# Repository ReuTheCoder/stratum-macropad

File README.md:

# Stratum 
Stratum is a 9-key personal macropad creation with a rotary encoder, an OLED display and RGB backlighting under each key that uses QMK firmware. It supports five independent layers, allowing each key to perform a unique function depending on the active layer. Stratum was made as a submission for [Hackpad v5](https://hackpad.hackclub.com/) through HackClub's Stardance Challenge.

## Features:
- 0.91 inch OLED display
- A EC11 Rotary encoder (push button diabled)
- 9 MX-Style switches with DSA keycaps
- 9 accompanying SK6812 MINI-E LEDs for backlighting

## PCB
This is the PCB I made for Stratum; made in KiCad 10.0. Most of the footprints were provided by HackClub. Anything else was from KICad's default libraries or was sourced through peers on the HackClub Slack. The silkscreen uses HackClub's logo and a character from the Stardance Challenge.

**Schematic:**

**PCB:**

## CAD Model
This CAD model, designed in Fusion 360, utilizes an integrated plate keyboard mount style - so it only has a top and bottom piece that are connected together with four 16mm M3 bolts that are screwed in from the bottom of the case. Right now, the case relies on self-threading since I don't anticipate needing to unscrew the macropad often after assembly. Realistically, I have noted I will need to add heat-set inserts in a future version to ensure its long-term survival. The rotary encoder cap was provided by HackClub. 

## Firmware Overview
The name Stratum reflects this macropad's ability to swap between 5 distinct layers through QMK firmware. This is done through a Settings mode in which you must hold down three center keys until the OLED displays a selection menu where you can use the rotary encoder to scroll through the 5 different layers. You select with the lower-right key. An overview of notable firmware features are:

- 5 Different Layers: Main, Productivity, Design, Scientific and Media. The keys and rotary encoder change functions on each mode
- The OLED that displays current layer, settings menu and a transition animation
- RGB Backlights change color on each layer
- A sleep and brightness control in settings
- Rotary encoder volume control

The 5 layers will likely be updated as I use the macropad and see what does and does not work. A future idea I have in mind is adding VIA support for quick macro functionality edits.

## Bill of Materials [BOM]:
All the components needed for this macropad design:
- 9x Cherry MX Switches
- 9x DSA Keycaps
- 4x M3x16mm screws
- 9x through-hole 1N4148 Diodes
- 9x SK6812 MINI-E LEDs (reverse mount)
- 1x 0.91 inch OLED display (128x32)
- 1x EC11 Rotary encoder
- 1x XIAO RP2040
- 1x Case (2 printed parts + optional Rotary Encoder Cap)
  
## Additional Notes
This was my first time completely designing a piece of hardware from scratch. I used this project as an opportunity to learn PCB design through KiCad (both things I have never done before) and become accustomed to a new CAD program (before this, I had only used Tinkercad for 3D printing). This project also served as an introduction to QMK firmware. Although this project greatly increased my understanding of it (as I already had some experience coding arduino in C++), I still need more time writing QMK firmware to become comfortably familiar with it (I had a lot of external help when writing my firmware). Although it seemed to compile correctly, I have no idea if it will work as expected once I flash it to the RP2040. 

### Firmware Layer-Specific Functions
Layer 0 - Main <br>
&emsp;       K1 Save | K2  (close/escape) | K3 Refresh <br>
&emsp;       K4 File Explorer | K5 Settings | K6 Task Manager <br>
&emsp;       K7 Emoji Panel | K8 Screenshot | K9 Calculator <br>

Layer 1 - Productivity (Docs) <br>
&emsp;    K1 Citations | K2  Spell Check| K3 Clear Formatting <br>
&emsp;     K4 Align Left| K5 Center | K6 Align Right <br>
&emsp;     K7 Find | K8 Insert Link| K9 Print <br>

Layer 2 -  Design <br>
&emsp;     K1 Undo | K2 Redo | K3 Duplicate <br>
&emsp;     K4 Group | K5 Ungroup | K6 Bring Forward <br>
&emsp;     K7 Zoom In | K8 Zoom Out  | K9 Fit Screen <br>

Layer 3 -  Scientific (Docs) <br>
&emsp;     K1 ° | K2 ±  | K3 × <br>
&emsp;     K4 √  |  K5 π  | K6 Σ <br>
&emsp;     K7 Superscript | K8 Subscript  | K9 Open Latex Editor <br>

Layer 4 -  Media <br>
&emsp;     K1 Play  | K2 Pause  | K3 Stop <br>
&emsp;     K4 Previous  |  K5 Next  | K6 Mute <br>
&emsp;     K7 Spotify | K8 Youtube | K9 Libby (Audiobook App) <br>

Thank you so much to @qcoral and the rest of the organizers of [Stardance](https://stardance.hackclub.com/missions/hackpad) and HackClub for this wonderful hardware exploration opportunity!

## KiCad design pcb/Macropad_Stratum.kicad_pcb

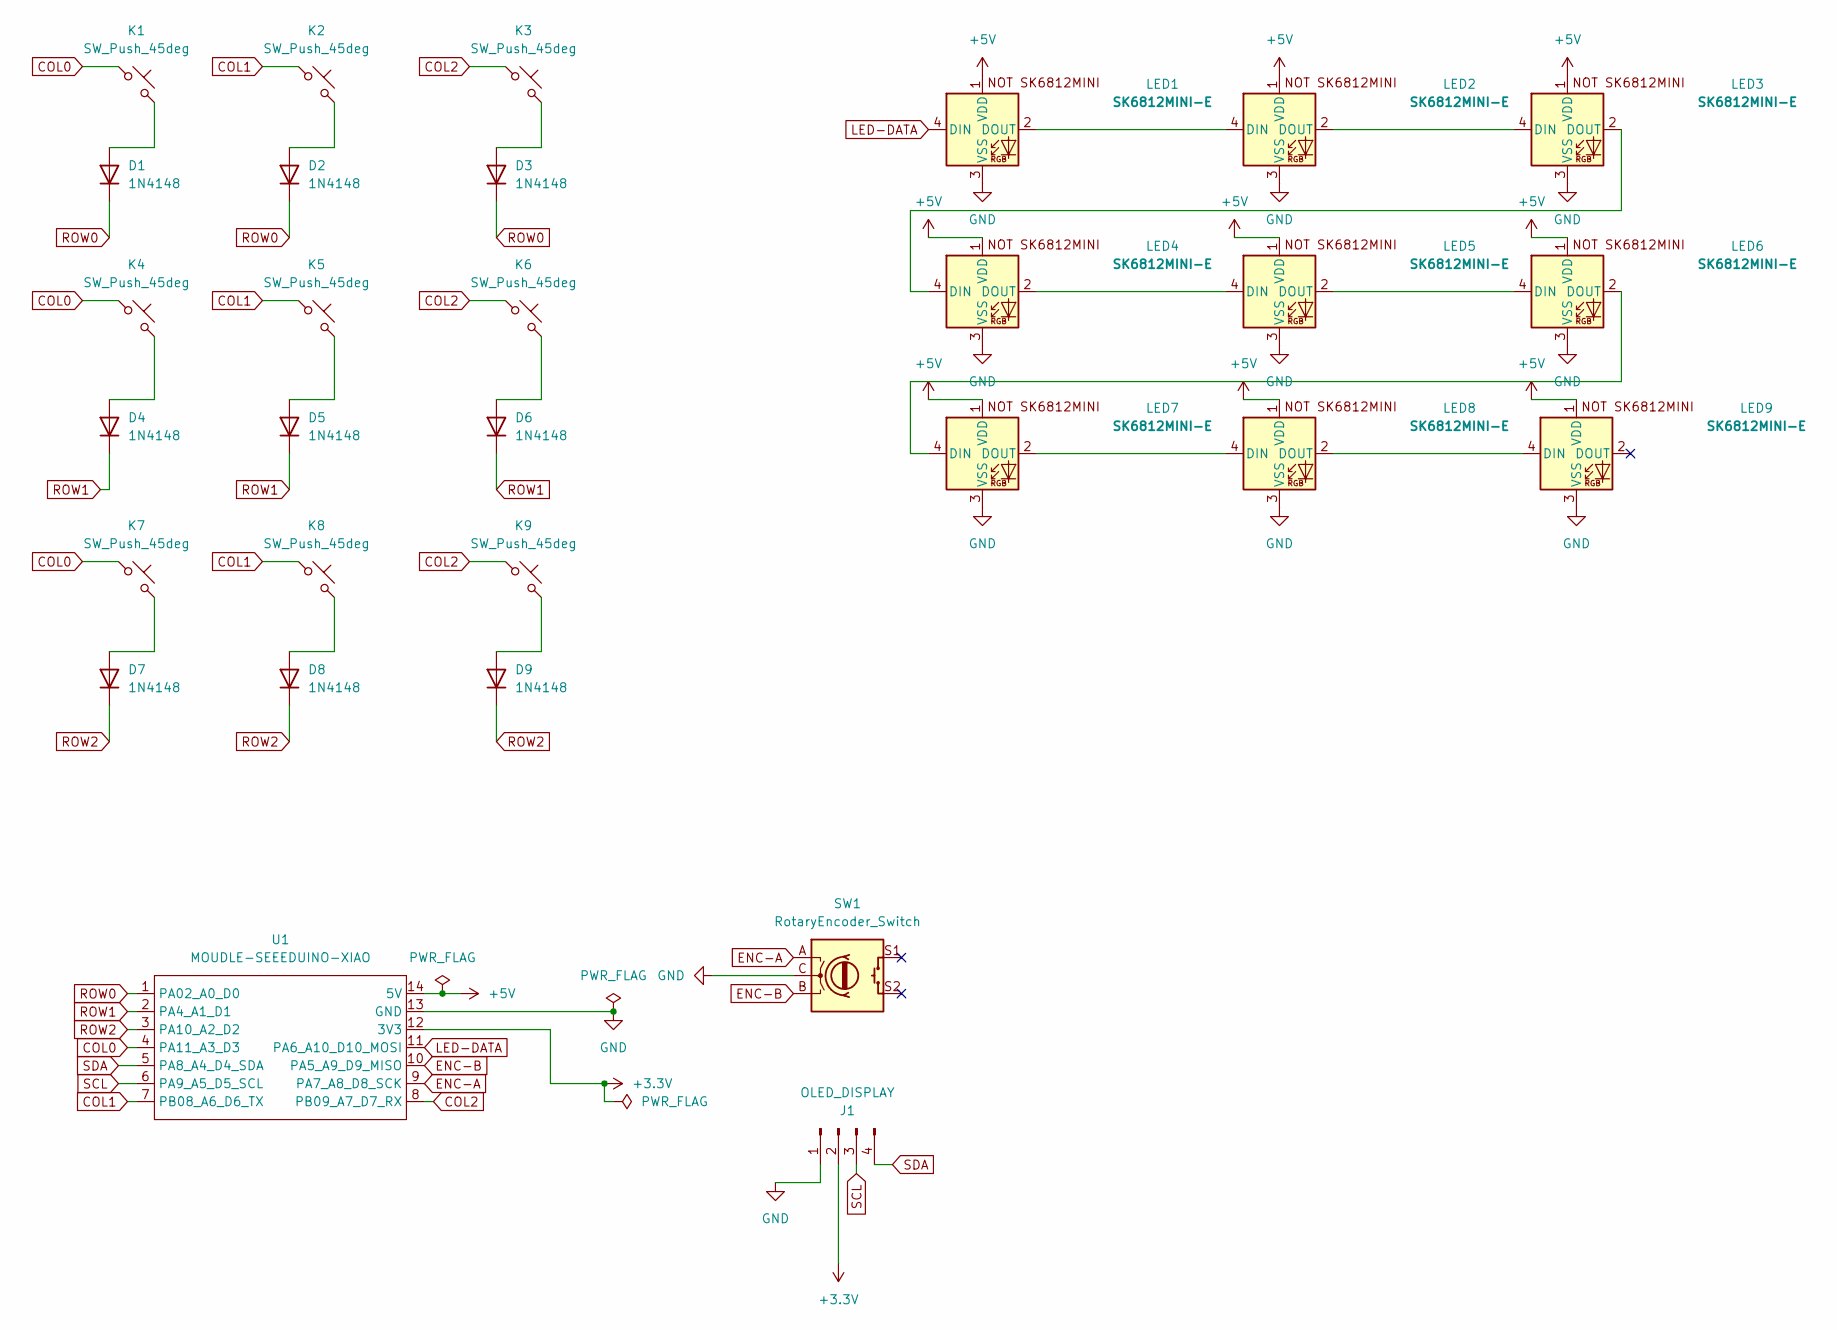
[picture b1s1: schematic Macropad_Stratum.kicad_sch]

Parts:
D1, D2, D3, D4, D5, D6, D7, D8, D9: 1N4148; D_DO-35_SOD27_P7.62mm_Horizontal
J1: OLED_DISPLAY; SSD1306-0.91-OLED-4pin-128x32
K1, K2, K3, K4, K5, K6, K7, K8, K9: SW_Push_45deg; SW_Cherry_MX_1.00u_PCB
LED1, LED2, LED3, LED4, LED5, LED6, LED7, LED8, LED9: SK6812MINI-E; SK6812MINI-E_fixed
SW1: RotaryEncoder_Switch; RotaryEncoder_Alps_EC11E-Switch_Vertical_H20mm
U1: MOUDLE-SEEEDUINO-XIAO; XIAO-Generic-Hybrid-14P-2.54-21X17.8MM

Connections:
+3.3V: J1.2, U1.12 (3V3)
+5V: LED1.1 (VDD), LED2.1 (VDD), LED3.1 (VDD), LED4.1 (VDD), LED5.1 (VDD), LED6.1 (VDD), LED7.1 (VDD), LED8.1 (VDD), LED9.1 (VDD), U1.14 (5V)
COL0: K1.1, K4.1, K7.1, U1.4 (PA11_A3_D3)
COL1: K2.1, K5.1, K8.1, U1.7 (PB08_A6_D6_TX)
COL2: K3.1, K6.1, K9.1, U1.8 (PB09_A7_D7_RX)
ENC-A: SW1.A, U1.9 (PA7_A8_D8_SCK)
ENC-B: SW1.B, U1.10 (PA5_A9_D9_MISO)
GND: J1.1, LED1.3 (VSS), LED2.3 (VSS), LED3.3 (VSS), LED4.3 (VSS), LED5.3 (VSS), LED6.3 (VSS), LED7.3 (VSS), LED8.3 (VSS), LED9.3 (VSS), SW1.C, U1.13 (GND)
LED-DATA: LED1.4 (DIN), U1.11 (PA6_A10_D10_MOSI)
unnamed: D1.2 (A), K1.2
unnamed: D2.2 (A), K2.2
unnamed: D3.2 (A), K3.2
unnamed: D4.2 (A), K4.2
unnamed: D5.2 (A), K5.2
unnamed: D6.2 (A), K6.2
unnamed: D7.2 (A), K7.2
unnamed: D8.2 (A), K8.2
unnamed: D9.2 (A), K9.2
unnamed: LED1.2 (DOUT), LED2.4 (DIN)
unnamed: LED2.2 (DOUT), LED3.4 (DIN)
unnamed: LED3.2 (DOUT), LED4.4 (DIN)
unnamed: LED4.2 (DOUT), LED5.4 (DIN)
unnamed: LED5.2 (DOUT), LED6.4 (DIN)
unnamed: LED6.2 (DOUT), LED7.4 (DIN)
unnamed: LED7.2 (DOUT), LED8.4 (DIN)
unnamed: LED8.2 (DOUT), LED9.4 (DIN)
ROW0: D1.1 (K), D2.1 (K), D3.1 (K), U1.1 (PA02_A0_D0)
ROW1: D4.1 (K), D5.1 (K), D6.1 (K), U1.2 (PA4_A1_D1)
ROW2: D7.1 (K), D8.1 (K), D9.1 (K), U1.3 (PA10_A2_D2)
SCL: J1.3, U1.6 (PA9_A5_D5_SCL)
SDA: J1.4, U1.5 (PA8_A4_D4_SDA)

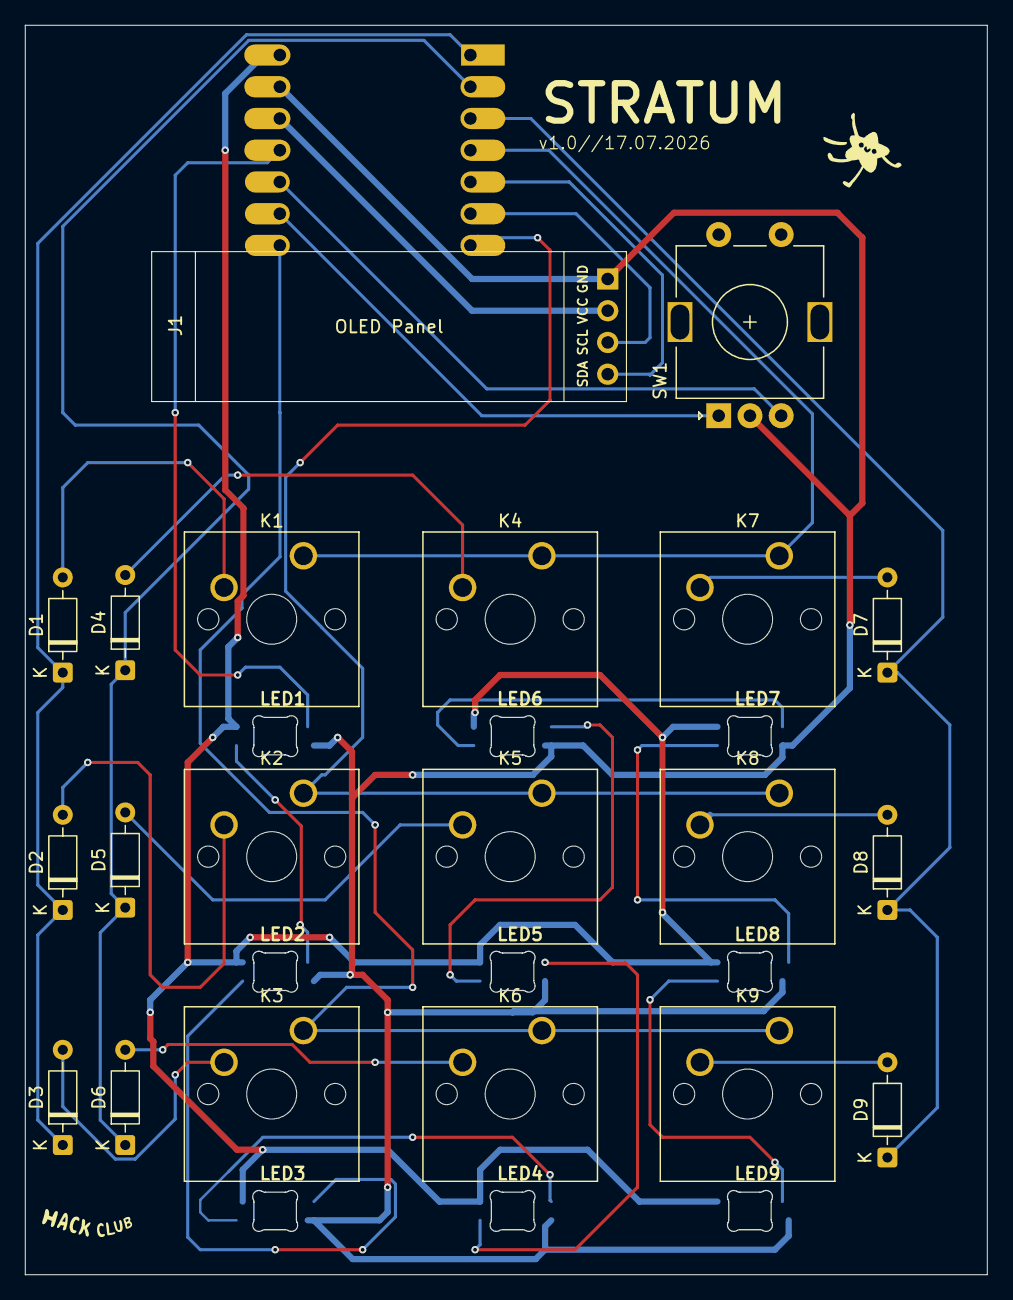
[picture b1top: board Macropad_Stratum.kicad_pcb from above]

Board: 2 copper layers, 77.0 x 100.0 mm, 30 parts (1 on the bottom side), 31 nets.
